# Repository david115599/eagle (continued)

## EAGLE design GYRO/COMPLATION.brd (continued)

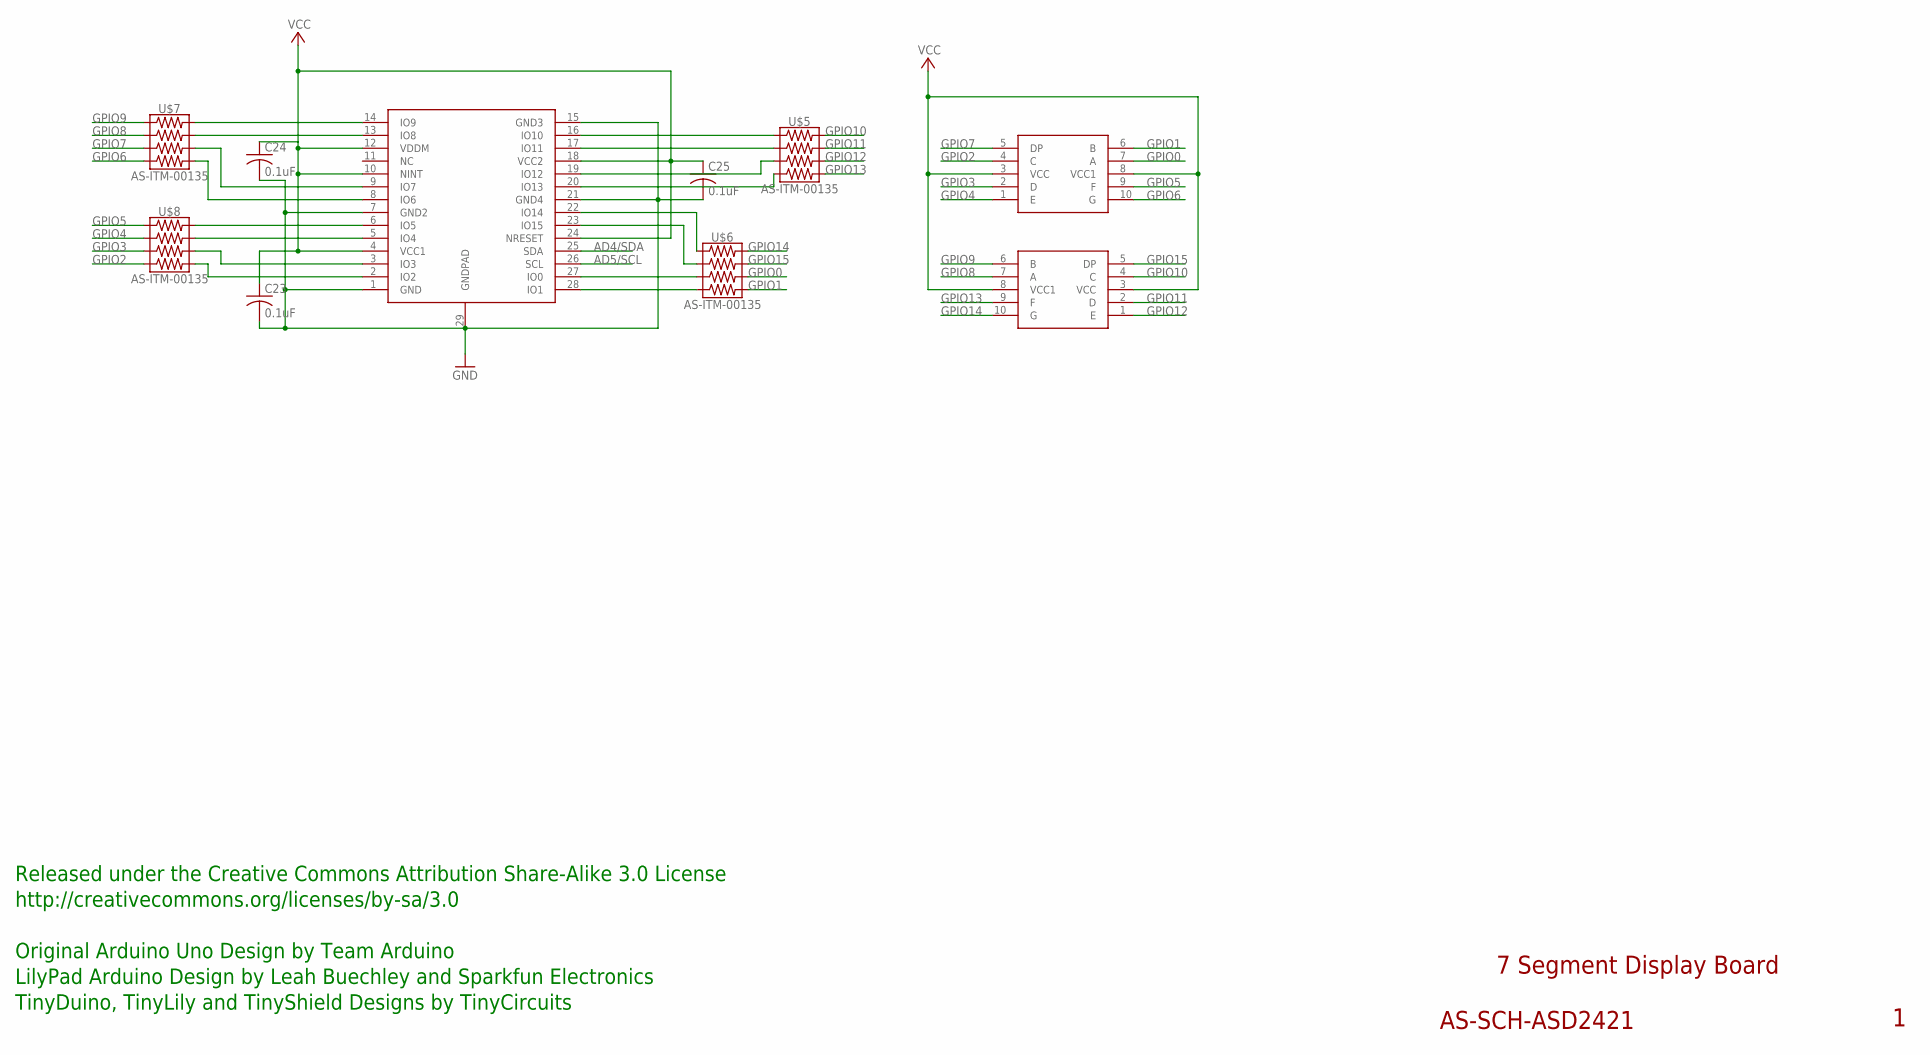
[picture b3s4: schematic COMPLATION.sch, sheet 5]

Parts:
C23, C24, C25: 0.1uF; C0402
U$2, U$3: AS-ITM-00133; ACSA02-41SURKWA-F01
U$4: AS-ITM-00134; SX1506
U$5, U$6, U$7, U$8: AS-ITM-00135; 0402RPACK

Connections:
AD4/SDA: U$4.25 (SDA); also elsewhere on the board
AD5/SCL: U$4.26 (SCL); also elsewhere on the board
GND: C23.2, C24.2, C25.2, U$4.1 (GND), U$4.7 (GND2), U$4.15 (GND3), U$4.21 (GND4), U$4.29 (GNDPAD); also elsewhere on the board
GPIO0: U$2.7 (A), U$6.6; also elsewhere on the board
GPIO1: U$2.6 (B), U$6.8; also elsewhere on the board
GPIO2: U$2.4 (C), U$8.7; also elsewhere on the board
GPIO3: U$2.2 (D), U$8.5; also elsewhere on the board
GPIO4: U$2.1 (E), U$8.3; also elsewhere on the board
GPIO5: U$2.9 (F), U$8.1; also elsewhere on the board
GPIO6: U$2.10 (G), U$7.7; also elsewhere on the board
GPIO7: U$2.5 (DP), U$7.5; also elsewhere on the board
GPIO8: U$3.7 (A), U$7.3; also elsewhere on the board
GPIO9: U$3.6 (B), U$7.1; also elsewhere on the board
GPIO10: U$3.4 (C), U$5.2; also elsewhere on the board
GPIO11: U$3.2 (D), U$5.4; also elsewhere on the board
GPIO12: U$3.1 (E), U$5.6; also elsewhere on the board
GPIO13: U$3.9 (F), U$5.8; also elsewhere on the board
GPIO14: U$3.10 (G), U$6.2; also elsewhere on the board
GPIO15: U$3.5 (DP), U$6.4; also elsewhere on the board
unnamed: U$4.14 (IO9), U$7.2
unnamed: U$4.13 (IO8), U$7.4
unnamed: U$4.9 (IO7), U$7.6
unnamed: U$4.8 (IO6), U$7.8
unnamed: U$4.6 (IO5), U$8.2
unnamed: U$4.5 (IO4), U$8.4
unnamed: U$4.3 (IO3), U$8.6
unnamed: U$4.2 (IO2), U$8.8
unnamed: U$4.16 (IO10), U$5.1
unnamed: U$4.17 (IO11), U$5.3
unnamed: U$4.19 (IO12), U$5.5
unnamed: U$4.20 (IO13), U$5.7
unnamed: U$4.22 (IO14), U$6.1
unnamed: U$4.23 (IO15), U$6.3
unnamed: U$4.27 (IO0), U$6.5
unnamed: U$4.28 (IO1), U$6.7
VCC: C23.1, C24.1, C25.1, U$2.3 (VCC), U$2.8 (VCC1), U$3.3 (VCC), U$3.8 (VCC1), U$4.4 (VCC1), U$4.10 (NINT), U$4.12 (VDDM), U$4.18 (VCC2), U$4.24 (NRESET); also elsewhere on the board

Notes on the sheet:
7 Segment Display Board
AS-SCH-ASD2421
Released under the Creative Commons Attribution Share-Alike 3.0 License
http://creativecommons.org/licenses/by-sa/3.0
LilyPad Arduino Design by Leah Buechley and Sparkfun Electronics
TinyDuino, TinyLily and TinyShield Designs by TinyCircuits
Original Arduino Uno Design by Team Arduino

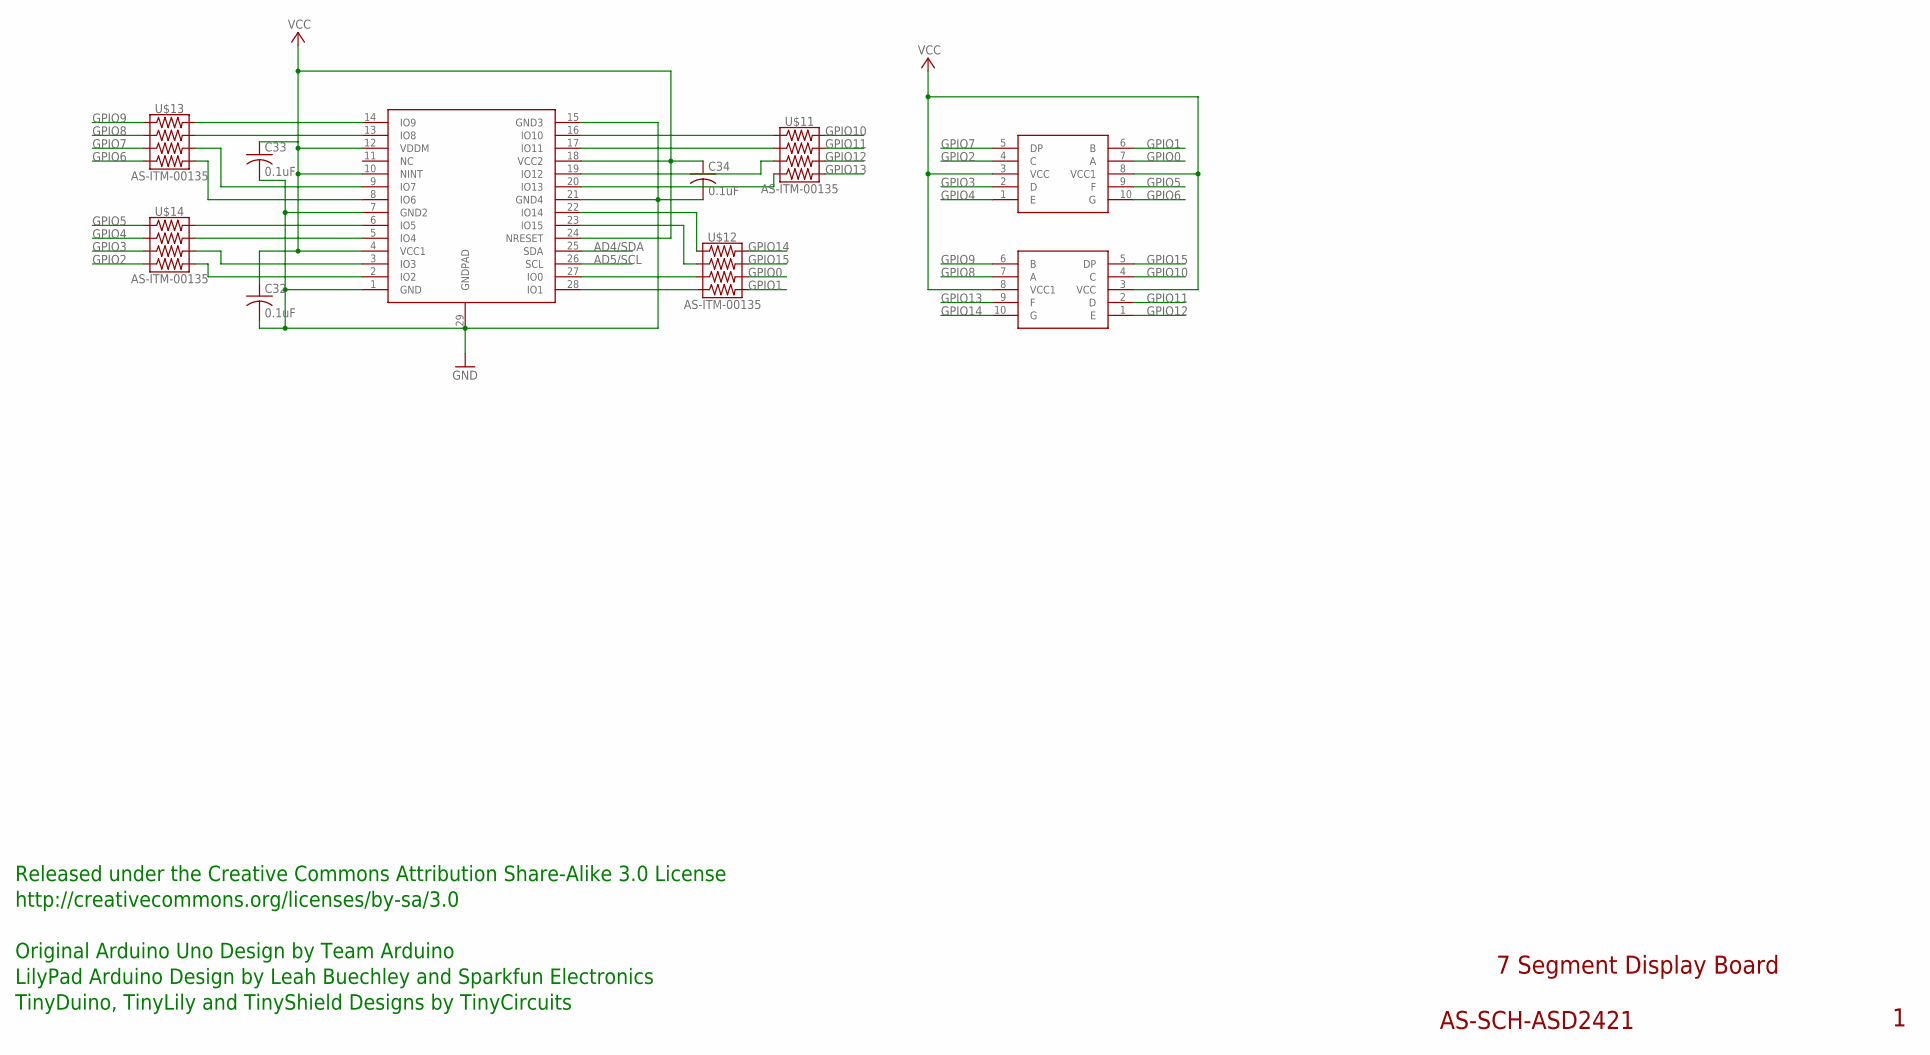
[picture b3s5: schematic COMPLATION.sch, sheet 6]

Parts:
C32, C33, C34: 0.1uF; C0402
U$1, U$9: AS-ITM-00133; ACSA02-41SURKWA-F01
U$10: AS-ITM-00134; SX1506
U$11, U$12, U$13, U$14: AS-ITM-00135; 0402RPACK

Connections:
AD4/SDA: U$10.25 (SDA); also elsewhere on the board
AD5/SCL: U$10.26 (SCL); also elsewhere on the board
GND: C32.2, C33.2, C34.2, U$10.1 (GND), U$10.7 (GND2), U$10.15 (GND3), U$10.21 (GND4), U$10.29 (GNDPAD); also elsewhere on the board
GPIO0: U$1.7 (A), U$12.6; also elsewhere on the board
GPIO1: U$1.6 (B), U$12.8; also elsewhere on the board
GPIO2: U$1.4 (C), U$14.7; also elsewhere on the board
GPIO3: U$1.2 (D), U$14.5; also elsewhere on the board
GPIO4: U$1.1 (E), U$14.3; also elsewhere on the board
GPIO5: U$1.9 (F), U$14.1; also elsewhere on the board
GPIO6: U$1.10 (G), U$13.7; also elsewhere on the board
GPIO7: U$1.5 (DP), U$13.5; also elsewhere on the board
GPIO8: U$9.7 (A), U$13.3; also elsewhere on the board
GPIO9: U$9.6 (B), U$13.1; also elsewhere on the board
GPIO10: U$9.4 (C), U$11.2; also elsewhere on the board
GPIO11: U$9.2 (D), U$11.4; also elsewhere on the board
GPIO12: U$9.1 (E), U$11.6; also elsewhere on the board
GPIO13: U$9.9 (F), U$11.8; also elsewhere on the board
GPIO14: U$9.10 (G), U$12.2; also elsewhere on the board
GPIO15: U$9.5 (DP), U$12.4; also elsewhere on the board
unnamed: U$10.14 (IO9), U$13.2
unnamed: U$10.13 (IO8), U$13.4
unnamed: U$10.9 (IO7), U$13.6
unnamed: U$10.8 (IO6), U$13.8
unnamed: U$10.6 (IO5), U$14.2
unnamed: U$10.5 (IO4), U$14.4
unnamed: U$10.3 (IO3), U$14.6
unnamed: U$10.2 (IO2), U$14.8
unnamed: U$10.16 (IO10), U$11.1
unnamed: U$10.17 (IO11), U$11.3
unnamed: U$10.19 (IO12), U$11.5
unnamed: U$10.20 (IO13), U$11.7
unnamed: U$10.22 (IO14), U$12.1
unnamed: U$10.23 (IO15), U$12.3
unnamed: U$10.27 (IO0), U$12.5
unnamed: U$10.28 (IO1), U$12.7
VCC: C32.1, C33.1, C34.1, U$1.3 (VCC), U$1.8 (VCC1), U$9.3 (VCC), U$9.8 (VCC1), U$10.4 (VCC1), U$10.10 (NINT), U$10.12 (VDDM), U$10.18 (VCC2), U$10.24 (NRESET); also elsewhere on the board

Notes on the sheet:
7 Segment Display Board
AS-SCH-ASD2421
Released under the Creative Commons Attribution Share-Alike 3.0 License
http://creativecommons.org/licenses/by-sa/3.0
LilyPad Arduino Design by Leah Buechley and Sparkfun Electronics
TinyDuino, TinyLily and TinyShield Designs by TinyCircuits
Original Arduino Uno Design by Team Arduino

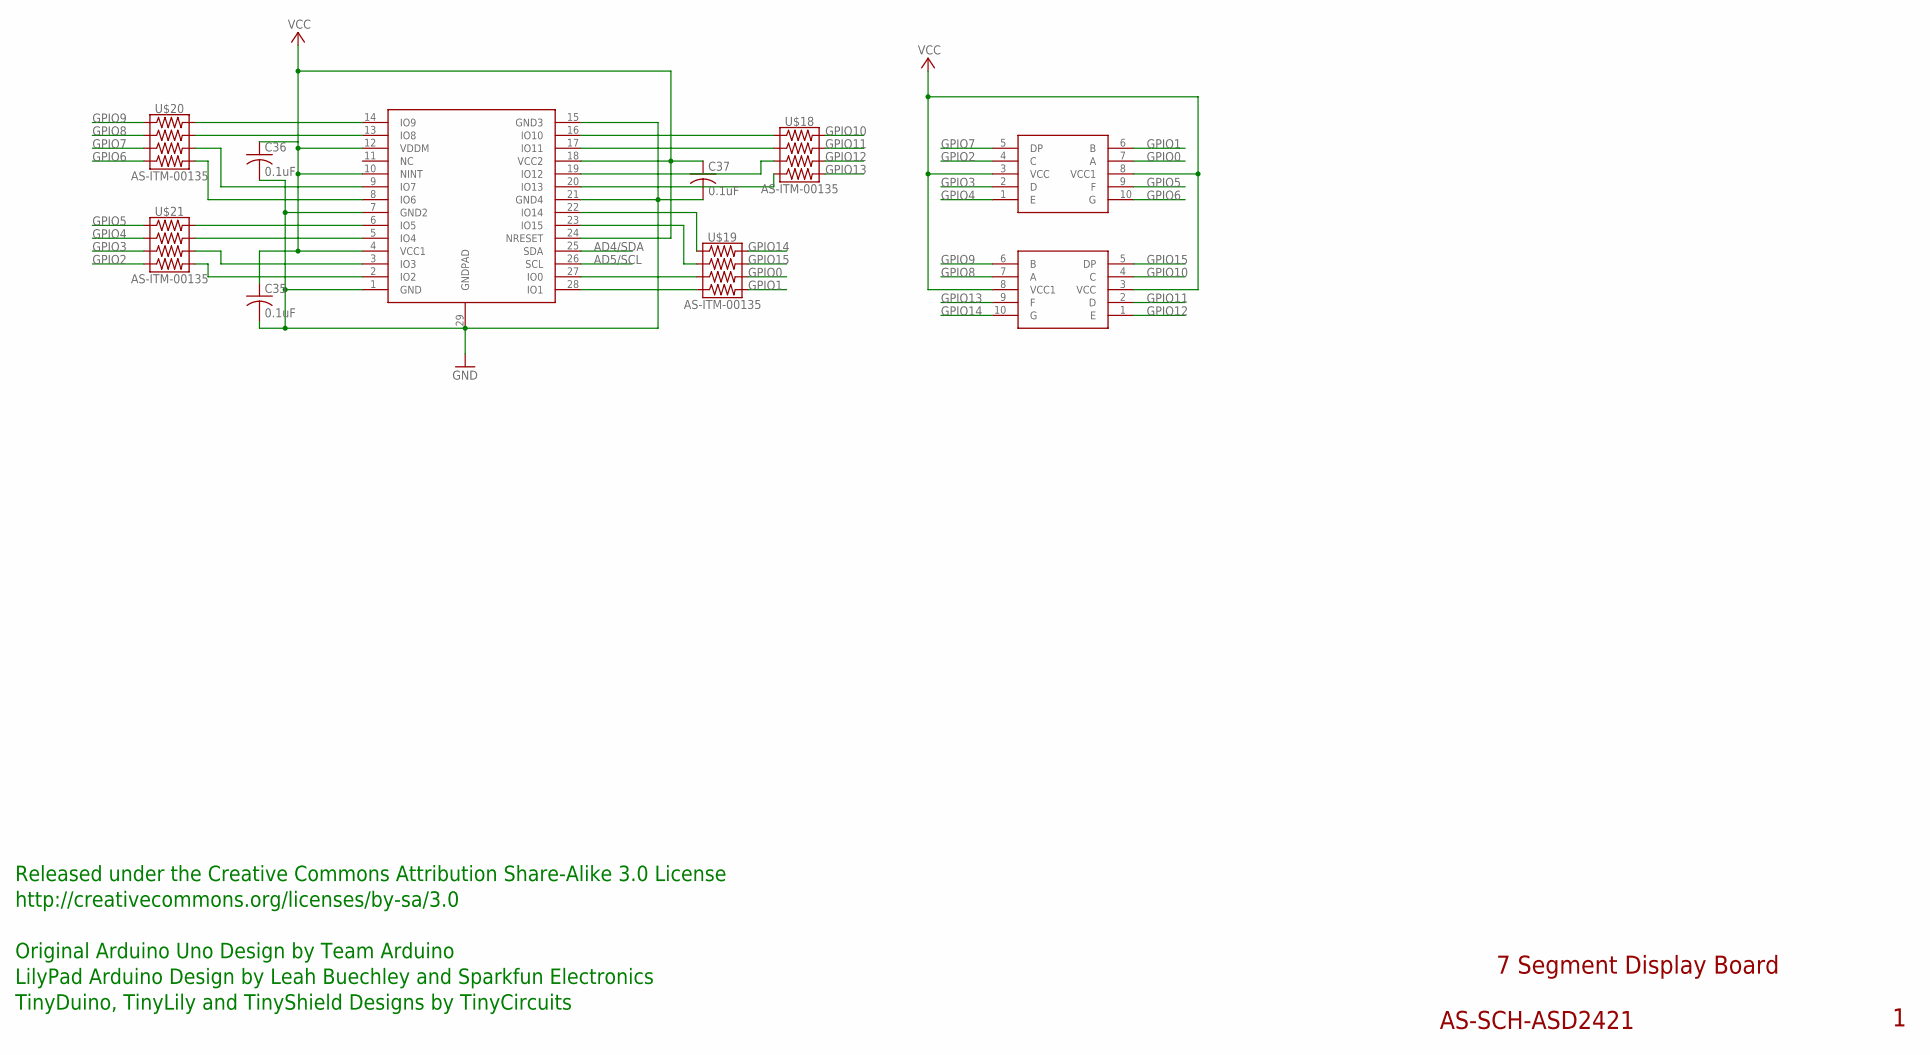
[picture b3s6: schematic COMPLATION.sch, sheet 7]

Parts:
C35, C36, C37: 0.1uF; C0402
U$15, U$16: AS-ITM-00133; ACSA02-41SURKWA-F01
U$17: AS-ITM-00134; SX1506
U$18, U$19, U$20, U$21: AS-ITM-00135; 0402RPACK

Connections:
AD4/SDA: U$17.25 (SDA); also elsewhere on the board
AD5/SCL: U$17.26 (SCL); also elsewhere on the board
GND: C35.2, C36.2, C37.2, U$17.1 (GND), U$17.7 (GND2), U$17.15 (GND3), U$17.21 (GND4), U$17.29 (GNDPAD); also elsewhere on the board
GPIO0: U$15.7 (A), U$19.6; also elsewhere on the board
GPIO1: U$15.6 (B), U$19.8; also elsewhere on the board
GPIO2: U$15.4 (C), U$21.7; also elsewhere on the board
GPIO3: U$15.2 (D), U$21.5; also elsewhere on the board
GPIO4: U$15.1 (E), U$21.3; also elsewhere on the board
GPIO5: U$15.9 (F), U$21.1; also elsewhere on the board
GPIO6: U$15.10 (G), U$20.7; also elsewhere on the board
GPIO7: U$15.5 (DP), U$20.5; also elsewhere on the board
GPIO8: U$16.7 (A), U$20.3; also elsewhere on the board
GPIO9: U$16.6 (B), U$20.1; also elsewhere on the board
GPIO10: U$16.4 (C), U$18.2; also elsewhere on the board
GPIO11: U$16.2 (D), U$18.4; also elsewhere on the board
GPIO12: U$16.1 (E), U$18.6; also elsewhere on the board
GPIO13: U$16.9 (F), U$18.8; also elsewhere on the board
GPIO14: U$16.10 (G), U$19.2; also elsewhere on the board
GPIO15: U$16.5 (DP), U$19.4; also elsewhere on the board
unnamed: U$17.14 (IO9), U$20.2
unnamed: U$17.13 (IO8), U$20.4
unnamed: U$17.9 (IO7), U$20.6
unnamed: U$17.8 (IO6), U$20.8
unnamed: U$17.6 (IO5), U$21.2
unnamed: U$17.5 (IO4), U$21.4
unnamed: U$17.3 (IO3), U$21.6
unnamed: U$17.2 (IO2), U$21.8
unnamed: U$17.16 (IO10), U$18.1
unnamed: U$17.17 (IO11), U$18.3
unnamed: U$17.19 (IO12), U$18.5
unnamed: U$17.20 (IO13), U$18.7
unnamed: U$17.22 (IO14), U$19.1
unnamed: U$17.23 (IO15), U$19.3
unnamed: U$17.27 (IO0), U$19.5
unnamed: U$17.28 (IO1), U$19.7
VCC: C35.1, C36.1, C37.1, U$15.3 (VCC), U$15.8 (VCC1), U$16.3 (VCC), U$16.8 (VCC1), U$17.4 (VCC1), U$17.10 (NINT), U$17.12 (VDDM), U$17.18 (VCC2), U$17.24 (NRESET); also elsewhere on the board

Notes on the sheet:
7 Segment Display Board
AS-SCH-ASD2421
Released under the Creative Commons Attribution Share-Alike 3.0 License
http://creativecommons.org/licenses/by-sa/3.0
LilyPad Arduino Design by Leah Buechley and Sparkfun Electronics
TinyDuino, TinyLily and TinyShield Designs by TinyCircuits
Original Arduino Uno Design by Team Arduino

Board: 2 copper layers, 107 parts (0 on the bottom side), 108 nets, no tracks yet.

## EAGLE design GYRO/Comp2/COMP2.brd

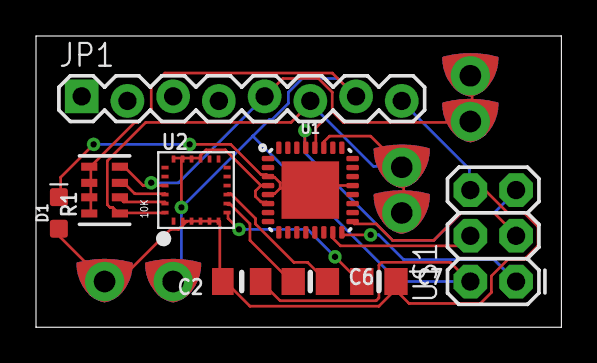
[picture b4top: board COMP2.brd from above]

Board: 2 copper layers, 29.2 x 16.2 mm, 15 parts (0 on the bottom side), 14 nets.

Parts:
C2: 10µF; 0805_10MGAP
C6: 0.22uF; 0805-NO
C7: 10uF; 0805-NO
D1: BLUE; LED-0603
GND: SEWTAP0.5IN; SEWINGTAP_0.5
JP1: 1X08_LOCK
R1: 10K; RESPACK_4X0603
SCL1, SCL2: SEWTAP0.5IN; SEWINGTAP_0.5
SDA1, SDA2: SEWTAP0.5IN; SEWINGTAP_0.5
U1: MLF32-PAD
U2: LSM9DS0TR; LGA24_4X4MM
U$1: AVR_SPI_PRG_6PTH; 2X3
VCC: SEWTAP0.5IN; SEWINGTAP_0.5

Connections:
GND: C2.2, C7.2, D1.A, GND.TAP, JP1.8, U2.2, U2.3, U2.4, U2.5, U2.6, U$1.6
MISO: U1.16, U$1.1
MOSI: U1.15, U$1.4
unnamed: C6.1, U2.8
unnamed: C6.2, U2.9
unnamed: D1.C, U1.3, U1.5, U1.21, U1.PAD
unnamed: C7.1, U2.7
RESET: U1.29, U$1.5
SA0_G: R1.3, U2.22
SA0_XM: R1.2, U2.23
SCK: U1.17, U$1.3
SCL: JP1.5, R1.4, SCL1.TAP, SCL2.TAP, U1.28, U2.21
SDA: JP1.6, R1.1, SDA1.TAP, SDA2.TAP, U1.27, U2.24
VCC: C2.1, JP1.7, R1.5, R1.6, R1.7, R1.8, U1.4, U1.6, U2.15, U2.16, U2.17, U2.18, U$1.2, VCC.TAP

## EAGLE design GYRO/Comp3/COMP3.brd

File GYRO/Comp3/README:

for comp 2 here are the required components that are orderd separatly
SparkFun Micro OLED Breakout
https://www.sparkfun.com/products/13003

Program the Arduino board through an ISP programmer such as https://www.pololu.com/product/1300

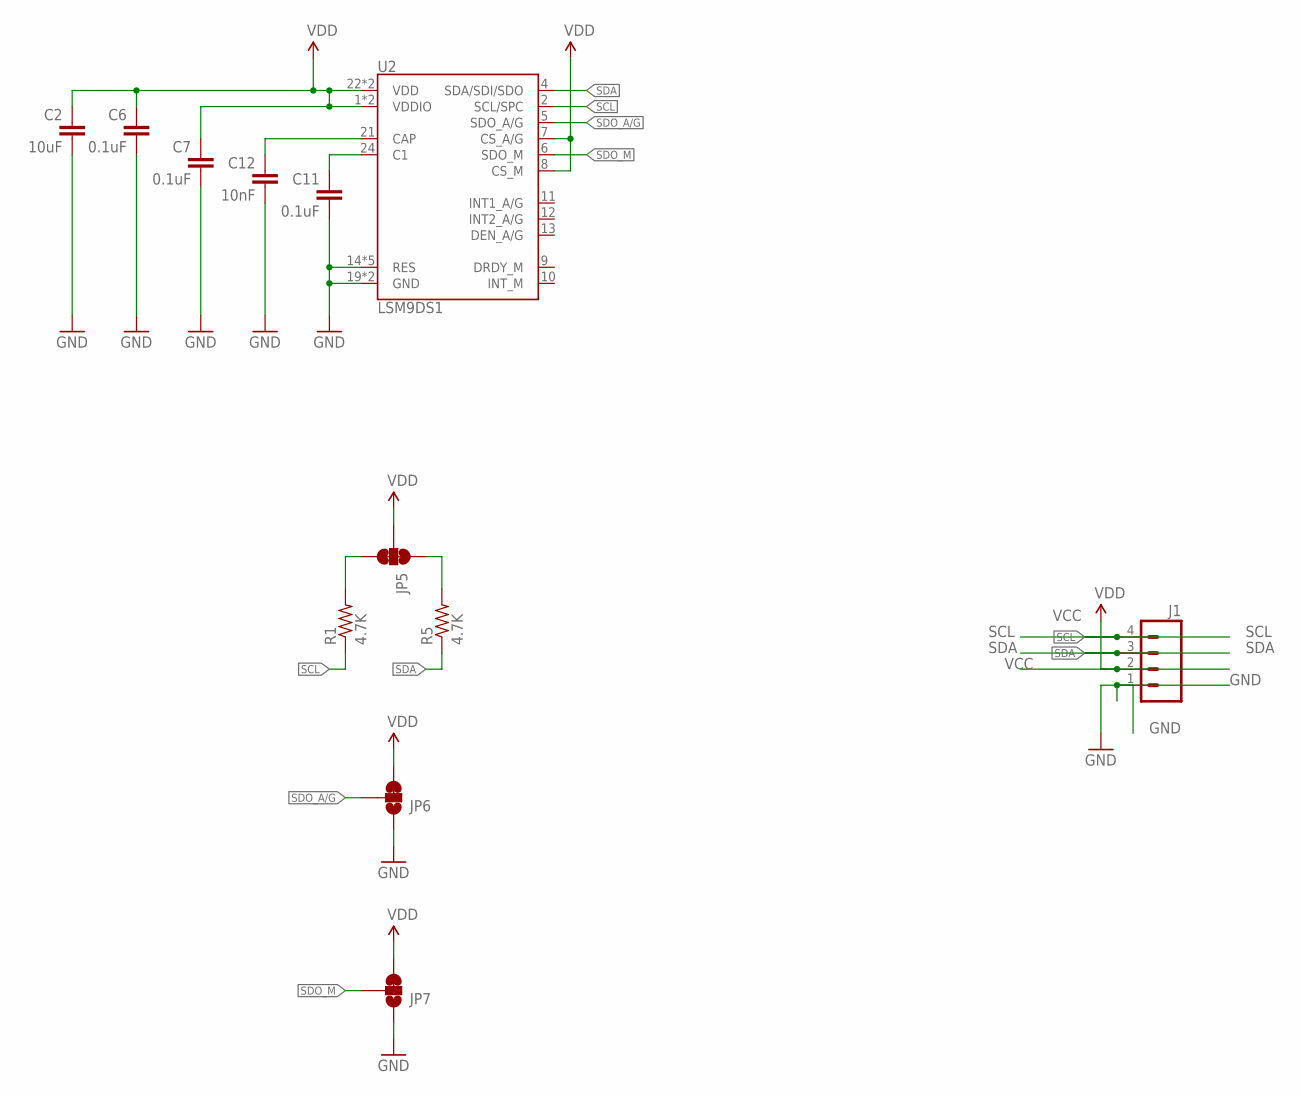
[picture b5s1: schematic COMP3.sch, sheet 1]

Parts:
C2: 10uF; 0603-CAP; MPN GRM188C81C106MA73D
C6, C7, C11: 0.1uF; 0603-CAP; MPN C0603C104K5RACAUTO
C12: 10nF; 0603-CAP; MPN EMK107SD103KA-T
J1: M04NO_SILK_ALL_ROUND; 1X04_NO_SILK_ALL_ROUND
JP5: JUMPER-PAD-3-NC_BY_TRACE; PAD-JUMPER-3-3OF3_NC_BY_TRACE_YES_SILK_FULL_BOX
JP6, JP7: JUMPER-PAD-3-2OF3_NC_BY_TRACE_SMALL; PAD-JUMPER-3-2OF3_NC_BY_TRACE_YES_SILK_FULL_BOX
R1, R5: 4.7K; 0603-RES; MPN M55342K12B4E70RS3
U2: LSM9DS1; LGA24-8X4; MPN LSM9DS1TR

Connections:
GND: C2.2, C6.2, C7.2, C11.2, C12.2, J1.1, JP6.1, JP7.1, U2.14 (RES), U2.15 (RES), U2.16 (RES), U2.17 (RES), U2.18 (RES), U2.19 (GND), U2.20 (GND); also elsewhere on the board
unnamed: JP5.1, R5.2
unnamed: JP5.3, R1.2
unnamed: C12.1, U2.21 (CAP)
unnamed: C11.1, U2.24 (C1)
SCL: J1.4, R1.1, U2.2 (SCL/SPC); also elsewhere on the board
SDA: J1.3, R5.1, U2.4 (SDA/SDI/SDO); also elsewhere on the board
SDO_A/G: JP6.2, U2.5 (SDO_A/G)
SDO_M: JP7.2, U2.6 (SDO_M)
VCC: C2.1, C6.1, C7.1, J1.2, JP5.2, JP6.3, JP7.3, U2.1 (VDDIO), U2.3 (VDDIO), U2.7 (CS_A/G), U2.8 (CS_M), U2.22 (VDD), U2.23 (VDD); also elsewhere on the board

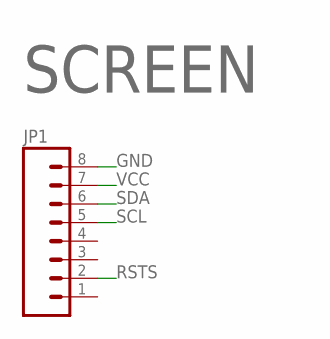
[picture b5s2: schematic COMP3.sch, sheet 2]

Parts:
JP1: M08LOCK; 1X08_LOCK

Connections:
GND: JP1.8; also elsewhere on the board
RSTS: JP1.2
SCL: JP1.5; also elsewhere on the board
SDA: JP1.6; also elsewhere on the board
VCC: JP1.7; also elsewhere on the board

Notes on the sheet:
SCREEN

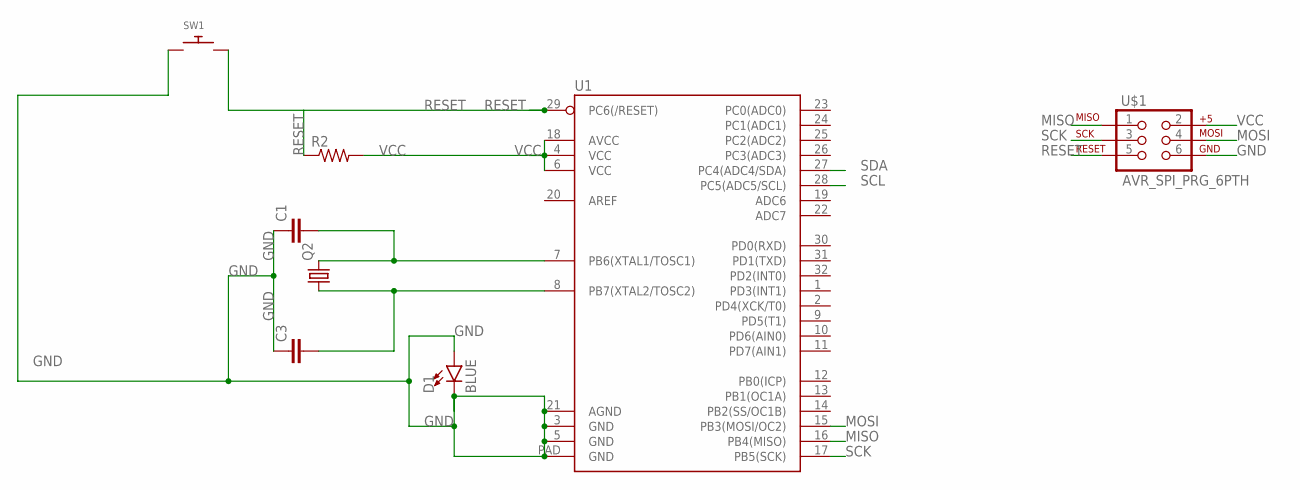
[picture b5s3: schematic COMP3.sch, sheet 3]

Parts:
C1, C3: C; C0805; MPN C0805C274K3RACTU
D1: BLUE; LED-0603; MPN HSMR-C120
Q2: CRYSTALHC49S; HC49/S; MPN X40M000000L104
R2: R-US_R0402; R0402; MPN CR0402-FX-1002GLF
SW1: SWITCH_PUSHBUTTONC&K_KSS; BTN_CK_KSS; MPN KSS221G LFS
U1: ATMEGA328P_MLFMLF32; MLF32-PAD; MPN ATMEGA8A-MU
U$1: AVR_SPI_PRG_6PTH; 2X3; MPN 1023

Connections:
GND: C1.1, C3.1, D1.A, D1.C, SW1.P$1, U1.3 (GND), U1.5 (GND), U1.21 (AGND), U1.PAD (GND), U$1.6; also elsewhere on the board
MISO: U1.16 (PB4(MISO)), U$1.1
MOSI: U1.15 (PB3(MOSI/OC2)), U$1.4
unnamed: C3.2, Q2.1, U1.8 (PB7(XTAL2/TOSC2))
unnamed: C1.2, Q2.2, U1.7 (PB6(XTAL1/TOSC1))
RESET: R2.1, SW1.P$2, U1.29 (PC6(/RESET)), U$1.5
SCK: U1.17 (PB5(SCK)), U$1.3
SCL: U1.28 (PC5(ADC5/SCL)); also elsewhere on the board
SDA: U1.27 (PC4(ADC4/SDA)); also elsewhere on the board
VCC: R2.2, U1.4 (VCC), U1.6 (VCC), U1.18 (AVCC), U$1.2; also elsewhere on the board

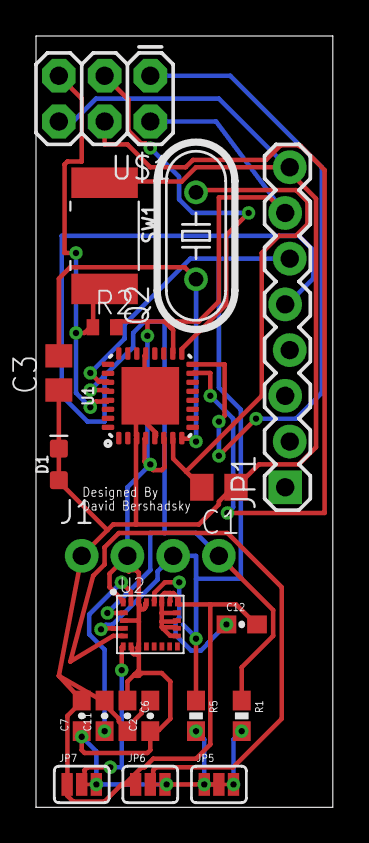
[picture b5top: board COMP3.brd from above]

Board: 2 copper layers, 16.5 x 42.8 mm, 21 parts (0 on the bottom side), 16 nets.

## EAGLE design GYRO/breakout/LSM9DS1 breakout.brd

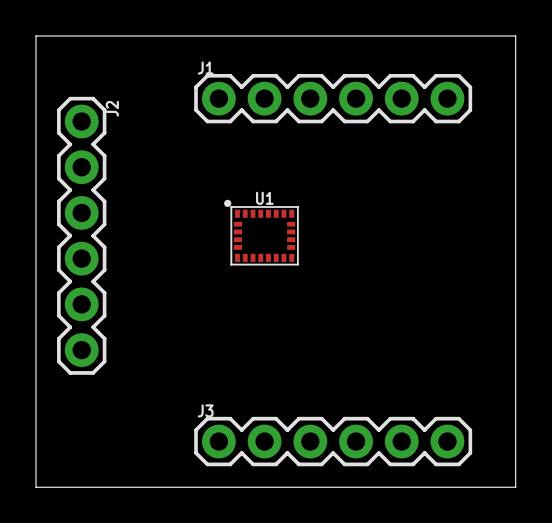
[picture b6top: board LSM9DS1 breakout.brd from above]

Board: 2 copper layers, 26.7 x 25.1 mm, 4 parts (0 on the bottom side), 17 nets, no tracks yet.

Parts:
J1, J2, J3: 1X06
U1: LSM9DS1; LGA-24-3.5X3

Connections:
unnamed: J1.6, U1.22, U1.23
unnamed: J1.5, U1.1, U1.3
unnamed: J1.4, U1.21
unnamed: J1.3, U1.24
unnamed: J1.2, U1.14, U1.15, U1.16, U1.17, U1.18
unnamed: J1.1, U1.19, U1.20
unnamed: J3.6, U1.10
unnamed: J3.5, U1.9
unnamed: J3.3, U1.13
unnamed: J3.2, U1.12
unnamed: J3.1, U1.11
unnamed: J2.6, U1.8
unnamed: J2.5, U1.6
unnamed: J2.4, U1.7
unnamed: J2.3, U1.5
unnamed: J2.2, U1.2
unnamed: J2.1, U1.4

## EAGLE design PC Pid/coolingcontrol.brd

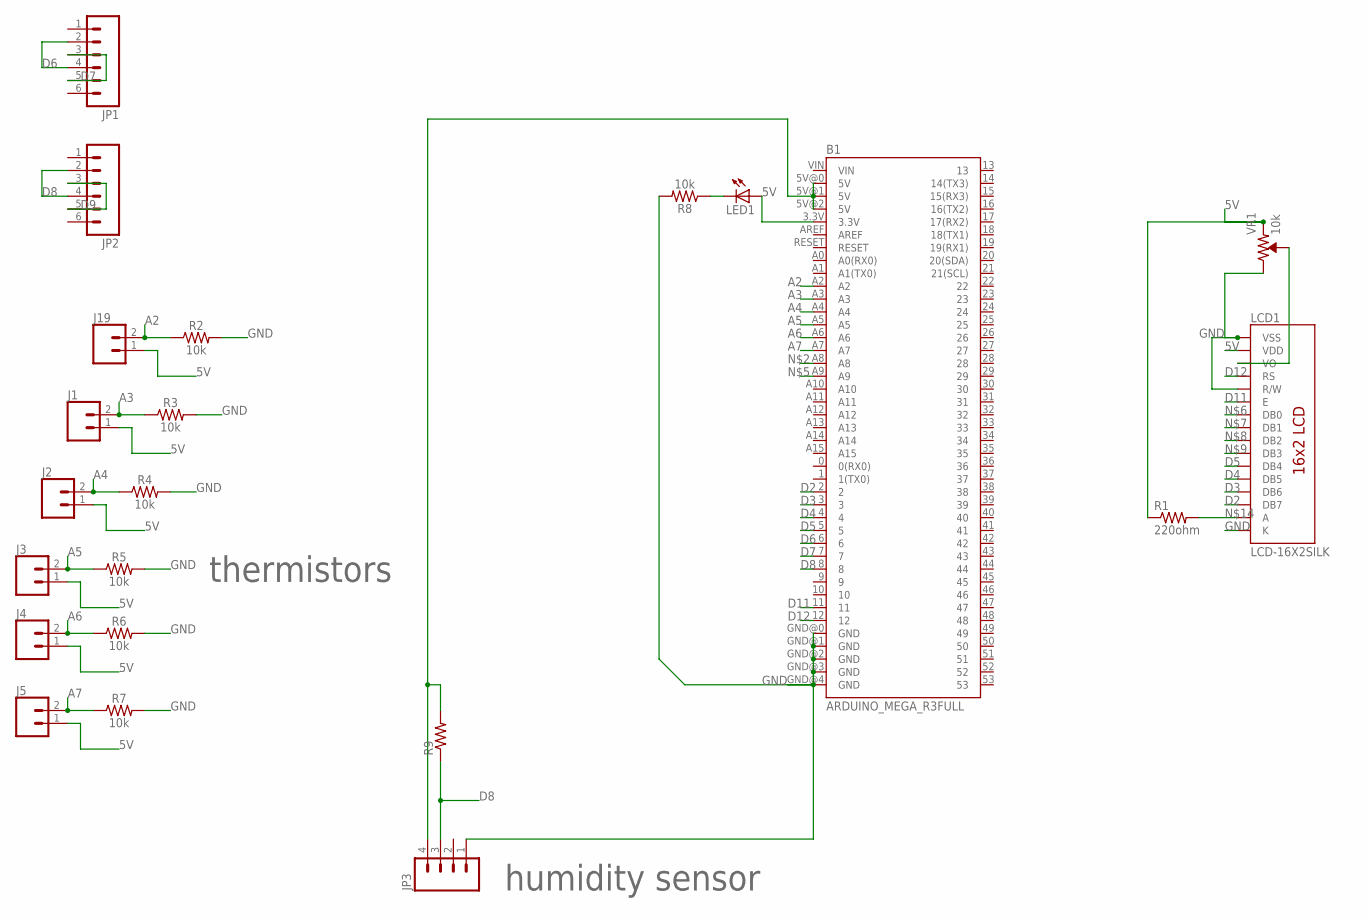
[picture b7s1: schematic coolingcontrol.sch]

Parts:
B1: ARDUINO_MEGA_R3FULL; ARDUINO_MEGA
J1, J2, J3, J4, J5, J19: CONN_02-JST-2-PTH-NO_SILK; JST-2-PTH-NS
JP1, JP2: M06POLAR; MOLEX-1X6
JP3: M04PTH; 1X04
LCD1: LCD-16X2SILK; LCD-16X2
LED1: LED5MM
R1: 220ohm; AXIAL-0.3
R2, R3, R4, R5, R6, R7, R8: 10k; AXIAL-0.3
R9: RESISTORPTH1; AXIAL-0.3
VR1: 10k; TRIMPOT-PTH-3386U

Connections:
5V: B1.5V@0 (5V), B1.5V@1 (5V), B1.5V@2 (5V), J1.1, J2.1, J3.1, J4.1, J5.1, J19.1, JP3.4, LCD1.2 (VDD), R1.P$1 (1), R9.P$2 (2), VR1.1 (CCW)
A2: B1.A2, J19.2, R2.P$1 (1)
A3: B1.A3, J1.2, R3.P$1 (1)
A4: B1.A4, J2.2, R4.P$1 (1)
A5: B1.A5, J3.2, R5.P$1 (1)
A6: B1.A6, J4.2, R6.P$1 (1)
A7: B1.A7, J5.2, R7.P$1 (1)
D2: B1.2, LCD1.14 (DB7)
D3: B1.3, LCD1.13 (DB6)
D4: B1.4, LCD1.12 (DB5)
D5: B1.5, LCD1.11 (DB4)
D6: B1.6, JP1.2, JP1.4
D7: B1.7, JP1.3, JP1.5
D8: B1.8, JP2.2, JP2.4, JP3.3, R9.P$1 (1)
D9: JP2.3, JP2.5
D11: B1.11, LCD1.6 (E)
D12: B1.12, LCD1.4 (RS)
GND: B1.GND@0 (GND), B1.GND@1 (GND), B1.GND@2 (GND), B1.GND@3 (GND), B1.GND@4 (GND), JP3.1, LCD1.1 (VSS), LCD1.5 (R/W), LCD1.16 (K), R2.P$2 (2), R3.P$2 (2), R4.P$2 (2), R5.P$2 (2), R6.P$2 (2), R7.P$2 (2), R8.P$2 (2), VR1.3 (CW)
unnamed: LCD1.3 (VO), VR1.2 (WIPER)
unnamed: LED1.K (C), R8.P$1 (1)
unnamed: B1.3.3V, LED1.A
unnamed: LCD1.15 (A), R1.P$2 (2)

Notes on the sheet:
thermistors
humidity sensor

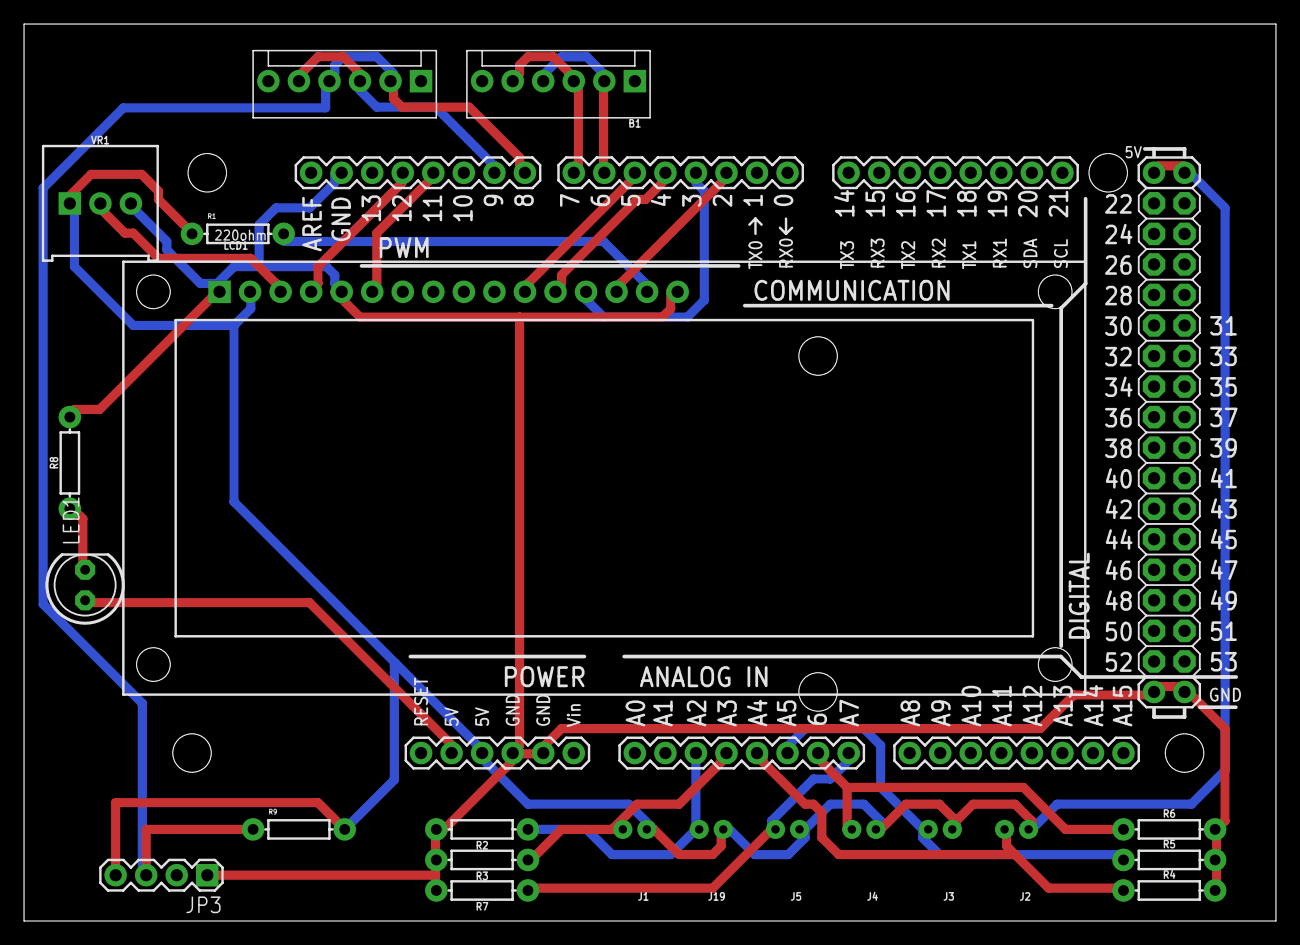
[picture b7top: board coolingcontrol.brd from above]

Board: 2 copper layers, 104.1 x 74.6 mm, 22 parts (0 on the bottom side), 22 nets.

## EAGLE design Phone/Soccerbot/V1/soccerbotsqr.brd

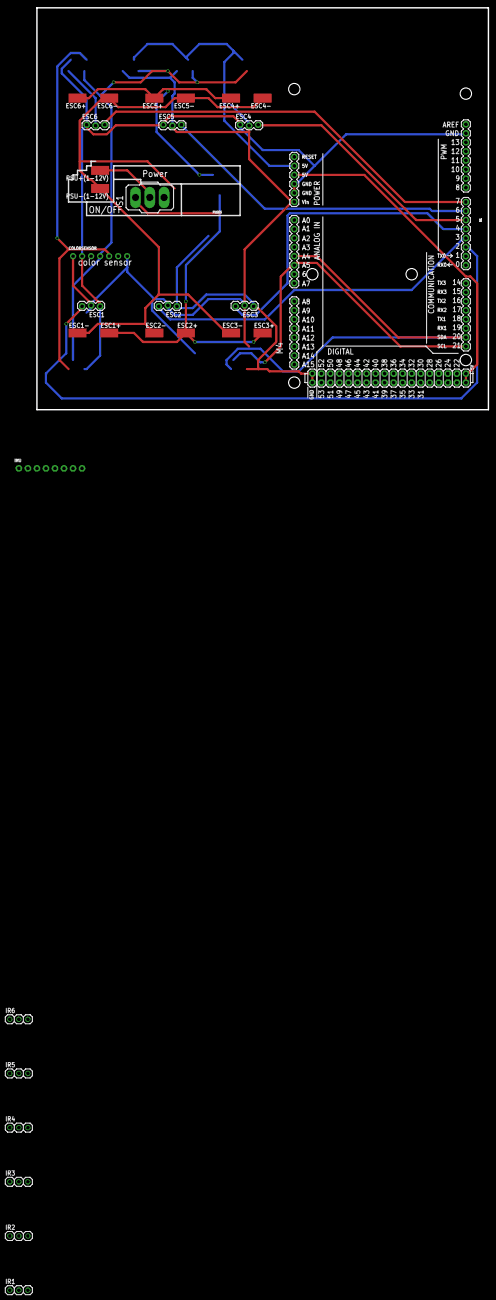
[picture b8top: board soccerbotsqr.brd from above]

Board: 2 copper layers, 127.0 x 113.0 mm, 30 parts (0 on the bottom side), 21 nets.

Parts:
B1: ARDUINO_MEGA_R3FULL; ARDUINO_MEGA
COLORSENSOR: 1X07_ROUND_70
ESC1, ESC2, ESC3, ESC4, ESC5, ESC6: 1X03_LOCK
ESC1+, ESC1-, ESC2+, ESC2-, ESC3+, ESC3-, ESC4+, ESC4-, ESC5+, ESC5-, ESC6+, ESC6-: SMD2,54-5,08
IMU: 1X08_ROUND_76
IR1, IR2, IR3, IR4, IR5, IR6: 1X03
PSU+(1-12V): SMD2,54-5,08
PSU-(1-12V): SMD2,54-5,08
S1: 320-916

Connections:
5.5V: B1.5V@0, B1.5V@1, B1.5V@2, IR1.3, IR2.3, IR3.3, IR4.3, IR5.3, IR6.3
+3V3: COLORSENSOR.3, IMU.8
BAT+: ESC1+.1, ESC2+.1, ESC3+.1, ESC4+.1, ESC5+.1, ESC6+.1, S1.1
BAT-: ESC1-.1, ESC2-.1, ESC3-.1, ESC4-.1, ESC5-.1, ESC6-.1, PSU-(1-12V).1
D2: B1.2, ESC1.3
D3: B1.3, ESC2.3
D4: B1.4, ESC3.3
D5: B1.5, ESC4.3
D6: B1.6, ESC5.3
D7: B1.7, ESC6.3
D8: B1.8, IR6.1
D9: B1.9, IR5.1
D10: B1.10, IR4.1
D11: B1.11, IR3.1
D12: B1.12, IR2.1
D13: B1.13, IR1.1
GND: B1.GND@0, B1.GND@1, B1.GND@2, B1.GND@3, B1.GND@4, COLORSENSOR.2, ESC1.1, ESC2.1, ESC3.1, ESC4.1, ESC5.1, ESC6.1, IMU.6, IR1.2, IR2.2, IR3.2, IR4.2, IR5.2, IR6.2
unnamed: PSU+(1-12V).1, S1.2
SCL: B1.21, B1.A5, COLORSENSOR.4, IMU.1
SDA: B1.20, B1.A4, COLORSENSOR.5, IMU.2
VIN: B1.VIN, COLORSENSOR.1, COLORSENSOR.7, ESC1.2, ESC2.2, ESC3.2, ESC4.2, ESC5.2, ESC6.2, IMU.7
